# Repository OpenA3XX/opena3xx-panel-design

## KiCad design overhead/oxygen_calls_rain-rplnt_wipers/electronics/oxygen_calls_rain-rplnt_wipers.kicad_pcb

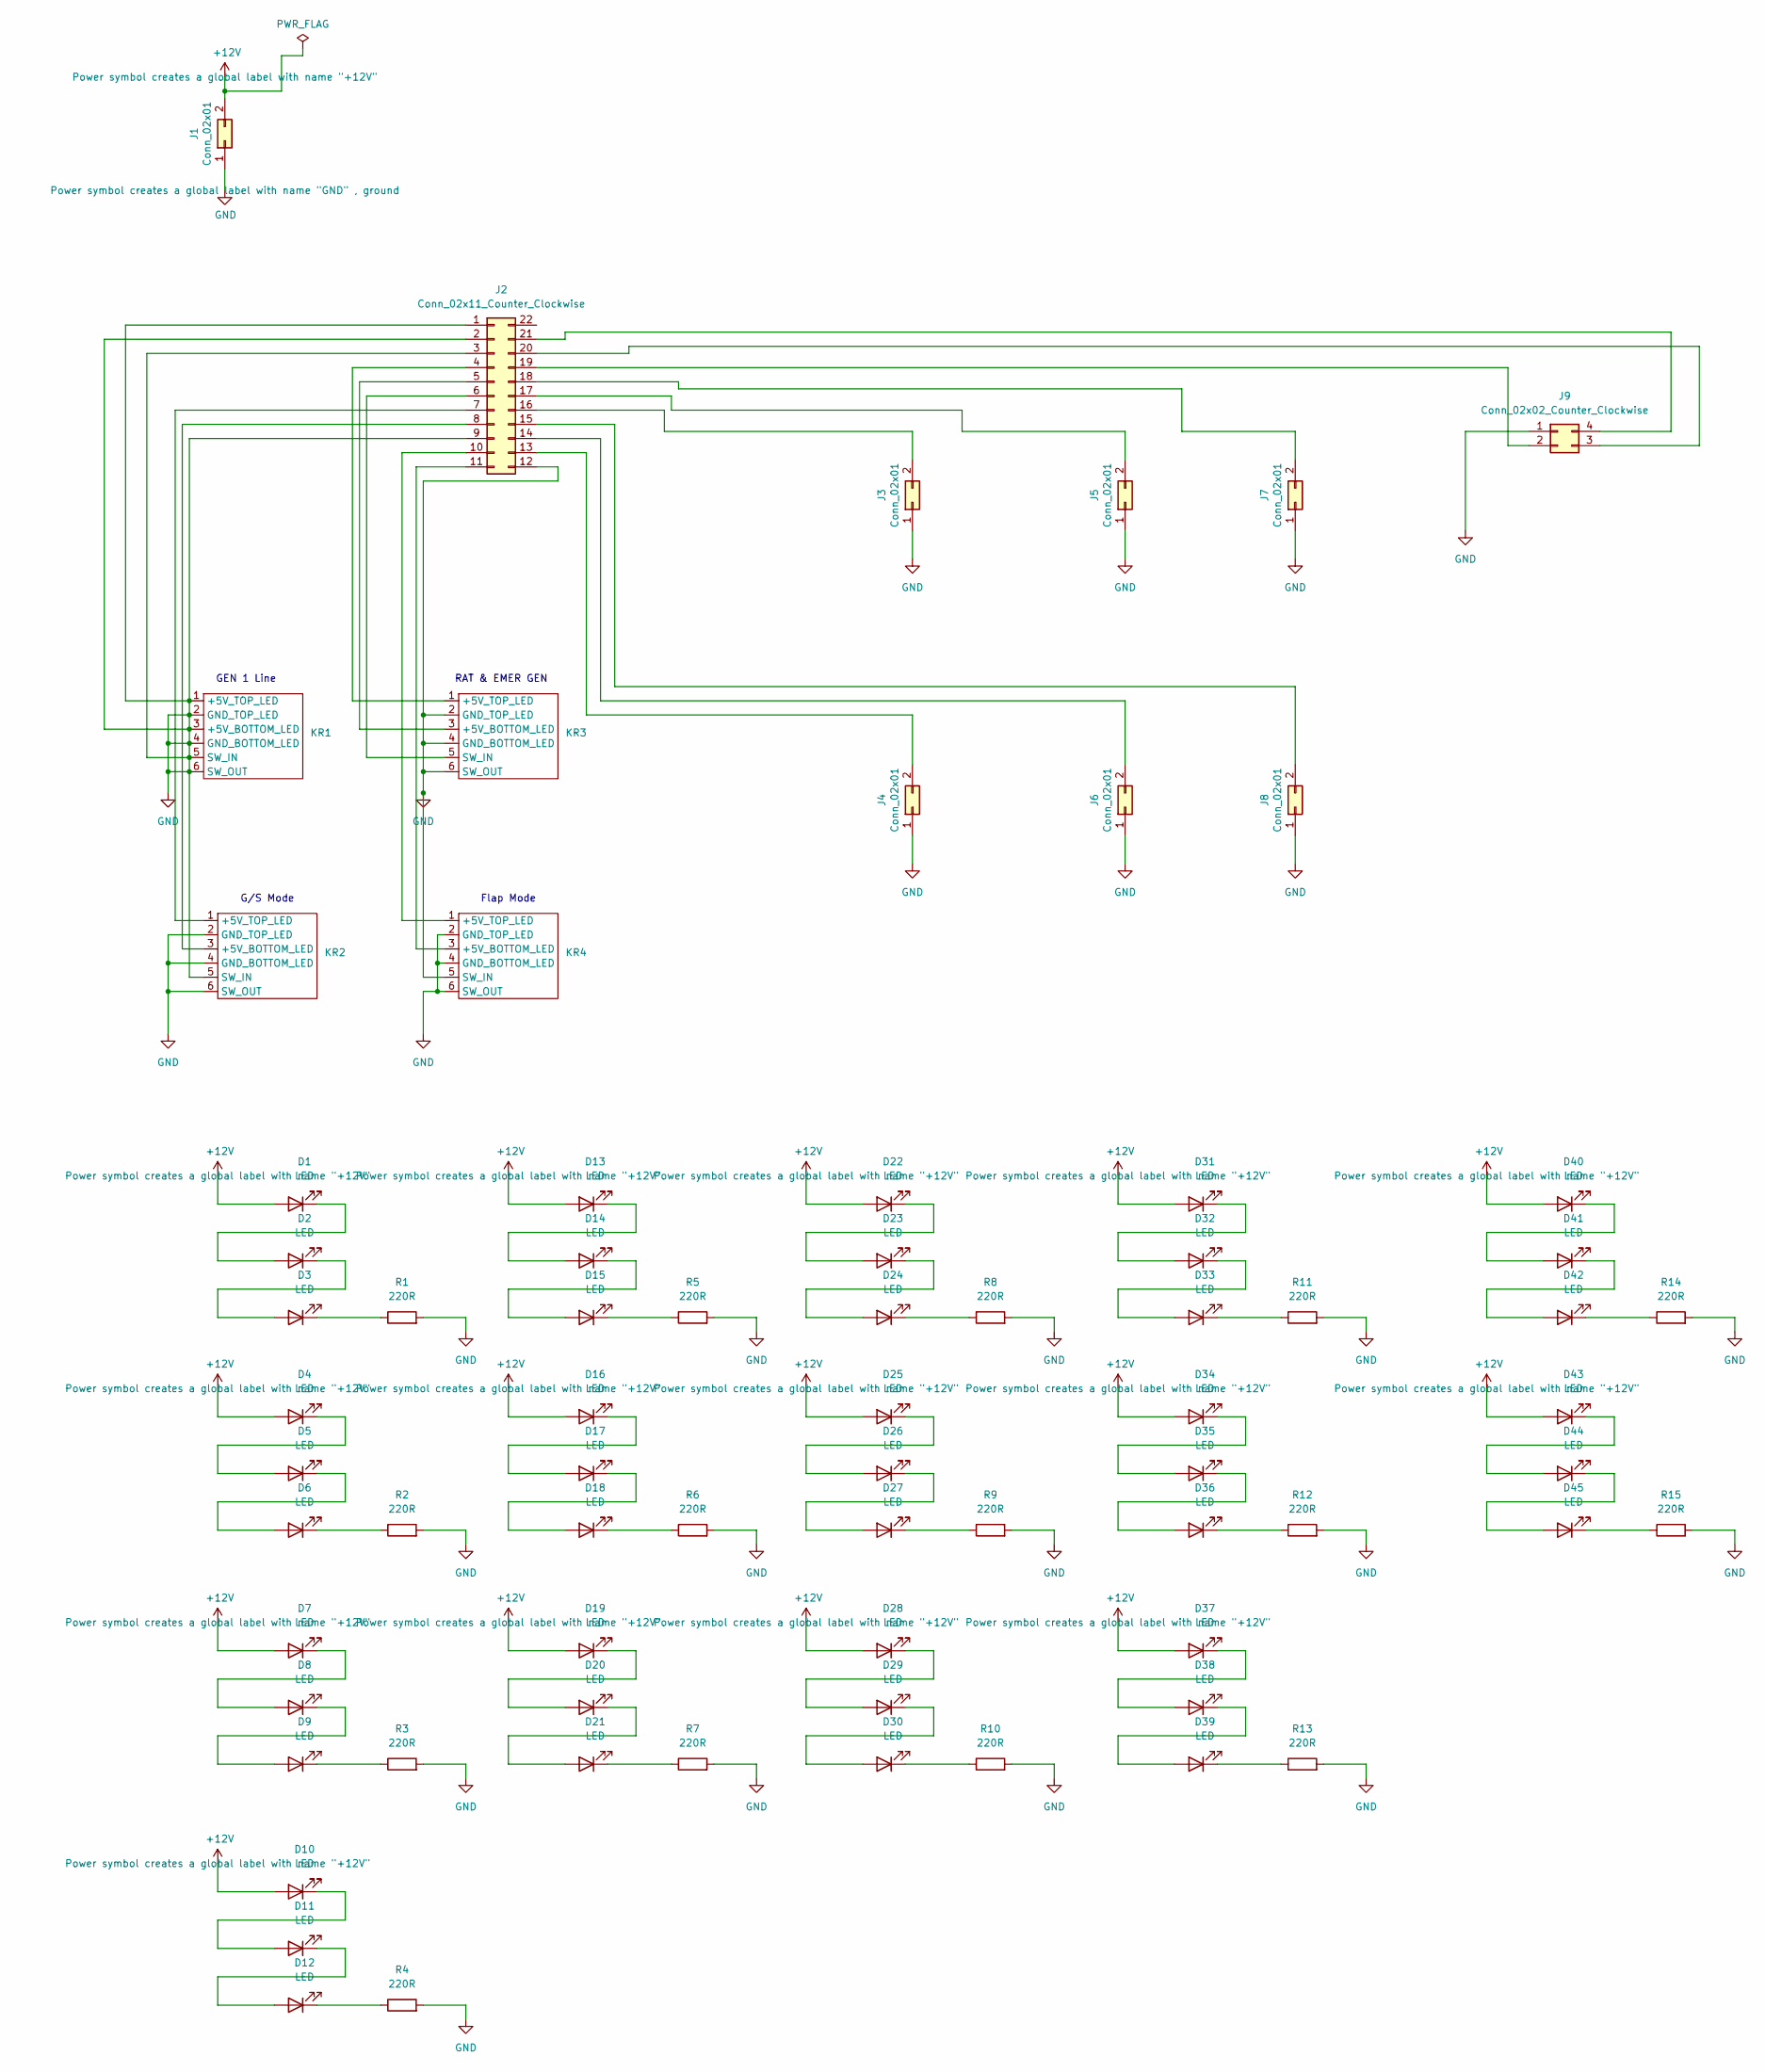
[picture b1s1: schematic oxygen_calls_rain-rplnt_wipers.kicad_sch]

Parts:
D1, D2, D3, D4, D5, D6, D7, D8, D9, D10, D11, D12, D13, D14, D15, D16, D17, D18, D19, D20, D21, D22, D23, D24, D25, D26, D27, D28, D29, D30, D31, D32, D33, D34, D35, D36, D37, D38, D39, D40, D41, D42, D43, D44, D45: LED; LED_Everlight-SMD3528_3.5x2.8mm_67-21ST
J1: Conn_02x01; TerminalBlock_bornier-2_P5.08mm
J2: Conn_02x11_Counter_Clockwise; PinHeader_2x11_P2.54mm_Vertical
J3, J4, J5, J6, J7, J8: Conn_02x01; PinHeader_1x02_P2.54mm_Vertical
J9: Conn_02x02_Counter_Clockwise; PinHeader_1x04_P2.54mm_Vertical
KR1, KR2, KR3, KR4: Korry Switch
R1, R2, R3, R4, R5, R6, R7, R8, R9, R10, R11, R12, R13, R14, R15: 220R; R_1206_3216Metric_Pad1.30x1.75mm_HandSolder

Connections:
+12V: D1.2 (A), D4.2 (A), D7.2 (A), D10.2 (A), D13.2 (A), D16.2 (A), D19.2 (A), D22.2 (A), D25.2 (A), D28.2 (A), D31.2 (A), D34.2 (A), D37.2 (A), D40.2 (A), D43.2 (A), J1.2
GND: J1.1, J2.1, J2.2, J2.3, J2.9, J2.12, J3.1, J4.1, J5.1, J6.1, J7.1, J8.1, J9.1, KR1.1 (+5V_TOP_LED), KR1.2 (GND_TOP_LED), KR1.3 (+5V_BOTTOM_LED), KR1.4 (GND_BOTTOM_LED), KR1.5 (SW_IN), KR1.6 (SW_OUT), KR2.2 (GND_TOP_LED), KR2.4 (GND_BOTTOM_LED), KR2.5 (SW_IN), KR2.6 (SW_OUT), KR3.2 (GND_TOP_LED), KR3.4 (GND_BOTTOM_LED), KR3.6 (SW_OUT), KR4.2 (GND_TOP_LED), KR4.4 (GND_BOTTOM_LED), KR4.5 (SW_IN), KR4.6 (SW_OUT), R1.2, R2.2, R3.2, R4.2, R5.2, R6.2, R7.2, R8.2, R9.2, R10.2, R11.2, R12.2, R13.2, R14.2, R15.2
unnamed: D1.1 (K), D2.2 (A)
unnamed: D2.1 (K), D3.2 (A)
unnamed: D3.1 (K), R1.1
unnamed: D4.1 (K), D5.2 (A)
unnamed: D5.1 (K), D6.2 (A)
unnamed: D6.1 (K), R2.1
unnamed: D7.1 (K), D8.2 (A)
unnamed: D8.1 (K), D9.2 (A)
unnamed: D9.1 (K), R3.1
unnamed: D10.1 (K), D11.2 (A)
unnamed: D11.1 (K), D12.2 (A)
unnamed: D12.1 (K), R4.1
unnamed: D13.1 (K), D14.2 (A)
unnamed: D14.1 (K), D15.2 (A)
unnamed: D15.1 (K), R5.1
unnamed: D16.1 (K), D17.2 (A)
unnamed: D17.1 (K), D18.2 (A)
unnamed: D18.1 (K), R6.1
unnamed: D19.1 (K), D20.2 (A)
unnamed: D20.1 (K), D21.2 (A)
unnamed: D21.1 (K), R7.1
unnamed: D22.1 (K), D23.2 (A)
unnamed: D23.1 (K), D24.2 (A)
unnamed: D24.1 (K), R8.1
unnamed: D25.1 (K), D26.2 (A)
unnamed: D26.1 (K), D27.2 (A)
unnamed: D27.1 (K), R9.1
unnamed: D28.1 (K), D29.2 (A)
unnamed: D29.1 (K), D30.2 (A)
unnamed: D30.1 (K), R10.1
unnamed: D31.1 (K), D32.2 (A)
unnamed: D32.1 (K), D33.2 (A)
unnamed: D33.1 (K), R11.1
unnamed: D34.1 (K), D35.2 (A)
unnamed: D35.1 (K), D36.2 (A)
unnamed: D36.1 (K), R12.1
unnamed: D37.1 (K), D38.2 (A)
unnamed: D38.1 (K), D39.2 (A)
unnamed: D39.1 (K), R13.1
unnamed: D40.1 (K), D41.2 (A)
unnamed: D41.1 (K), D42.2 (A)
unnamed: D42.1 (K), R14.1
unnamed: D43.1 (K), D44.2 (A)
unnamed: D44.1 (K), D45.2 (A)
unnamed: D45.1 (K), R15.1
unnamed: J2.4, KR3.1 (+5V_TOP_LED)
unnamed: J2.5, KR3.3 (+5V_BOTTOM_LED)
unnamed: J2.6, KR3.5 (SW_IN)
unnamed: J2.7, KR2.1 (+5V_TOP_LED)
unnamed: J2.8, KR2.3 (+5V_BOTTOM_LED)
unnamed: J2.10, KR4.1 (+5V_TOP_LED)
unnamed: J2.11, KR4.3 (+5V_BOTTOM_LED)
unnamed: J2.13, J4.2
unnamed: J2.14, J6.2
unnamed: J2.15, J8.2
unnamed: J2.16, J3.2
unnamed: J2.17, J5.2
unnamed: J2.18, J7.2
unnamed: J2.19, J9.2
unnamed: J2.20, J9.3
unnamed: J2.21, J9.4

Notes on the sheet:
G/S Mode
RAT & EMER GEN
GEN 1 Line
Flap Mode

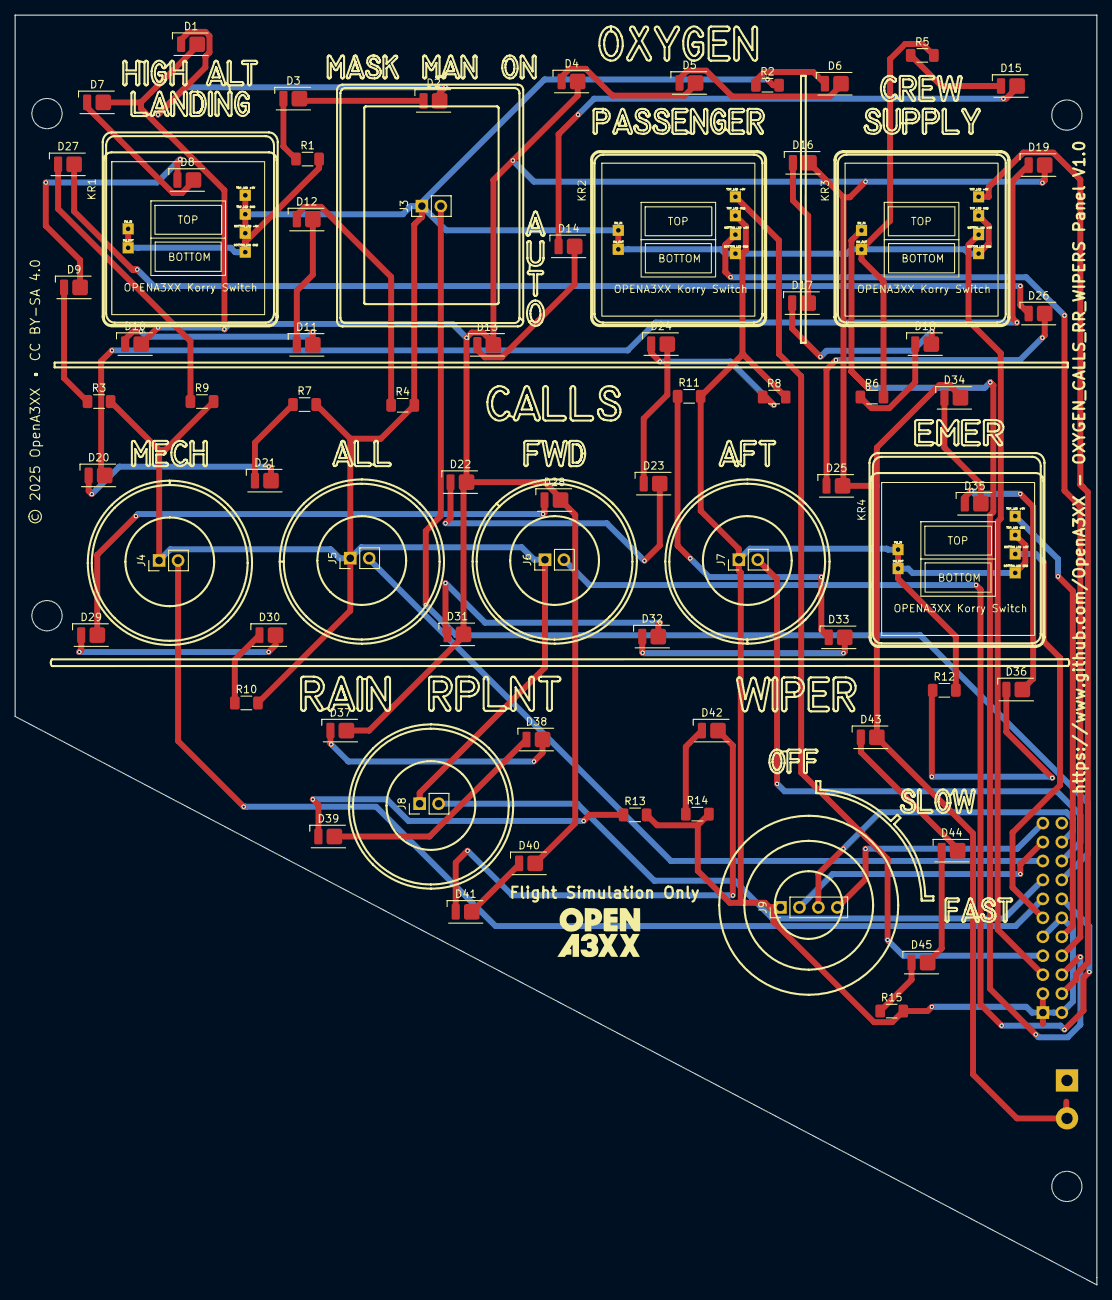
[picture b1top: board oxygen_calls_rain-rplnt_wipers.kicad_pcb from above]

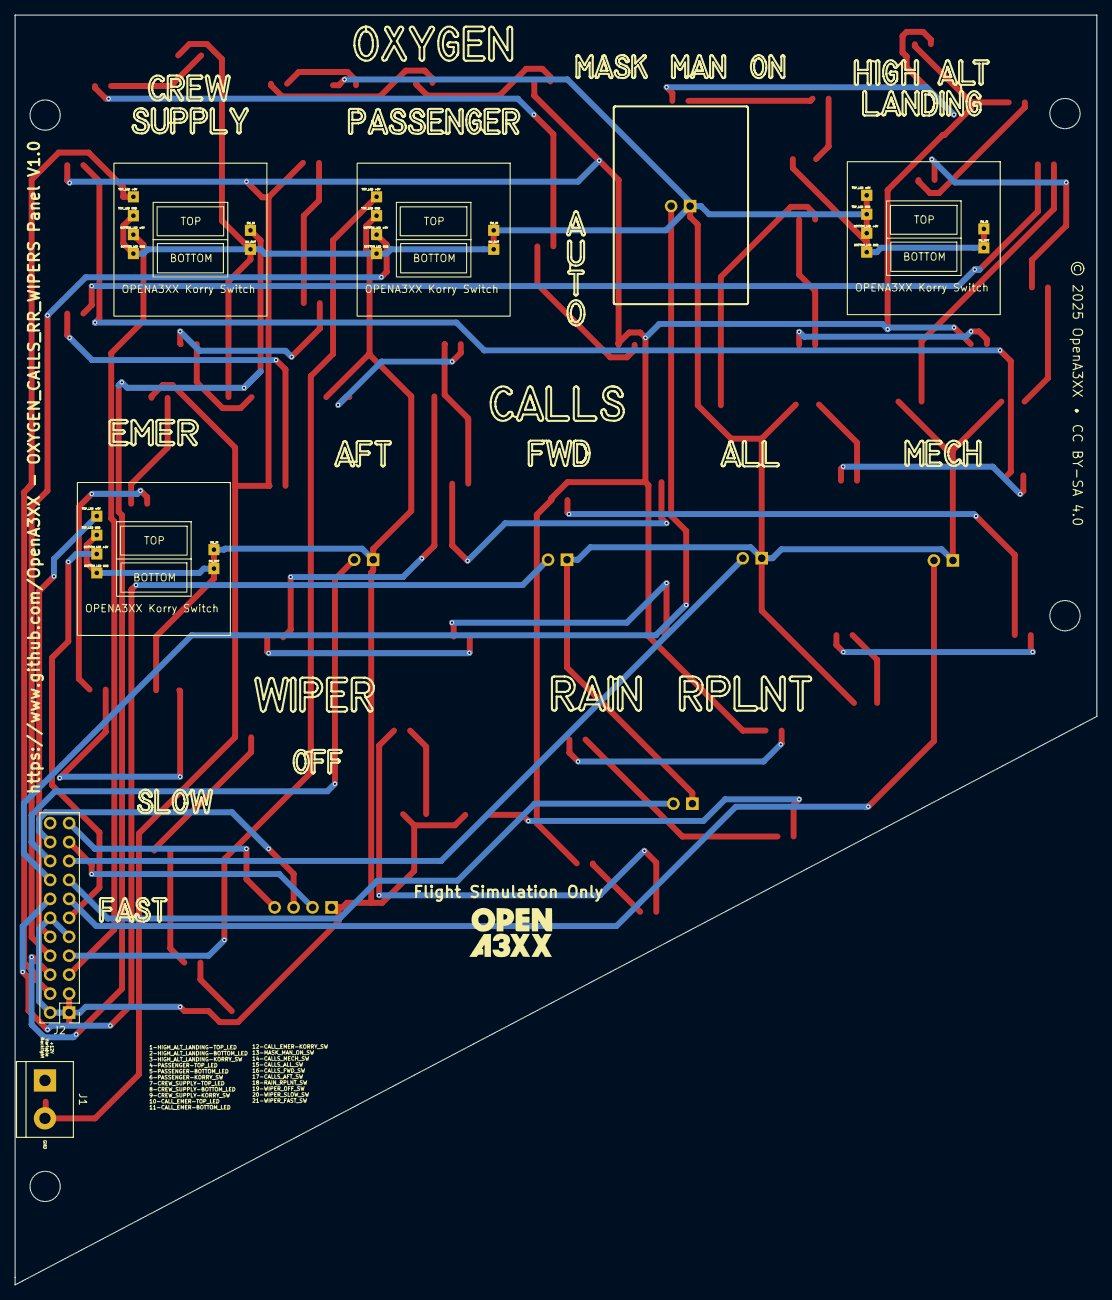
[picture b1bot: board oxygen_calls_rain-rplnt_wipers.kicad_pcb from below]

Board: 2 copper layers, 145.0 x 170.2 mm, 75 parts (3 on the bottom side), 63 nets.

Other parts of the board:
bottom: LOGO; OpenA3XXLogoSmall
top: LOGO; OpenA3XXLogoSmall

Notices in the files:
overhead/oxygen_calls_rain-rplnt_wipers/electronics/oxygen_calls_rain-rplnt_wipers.kicad_pcb:
© 2025 OpenA3XX • CC BY-SA 4.0
